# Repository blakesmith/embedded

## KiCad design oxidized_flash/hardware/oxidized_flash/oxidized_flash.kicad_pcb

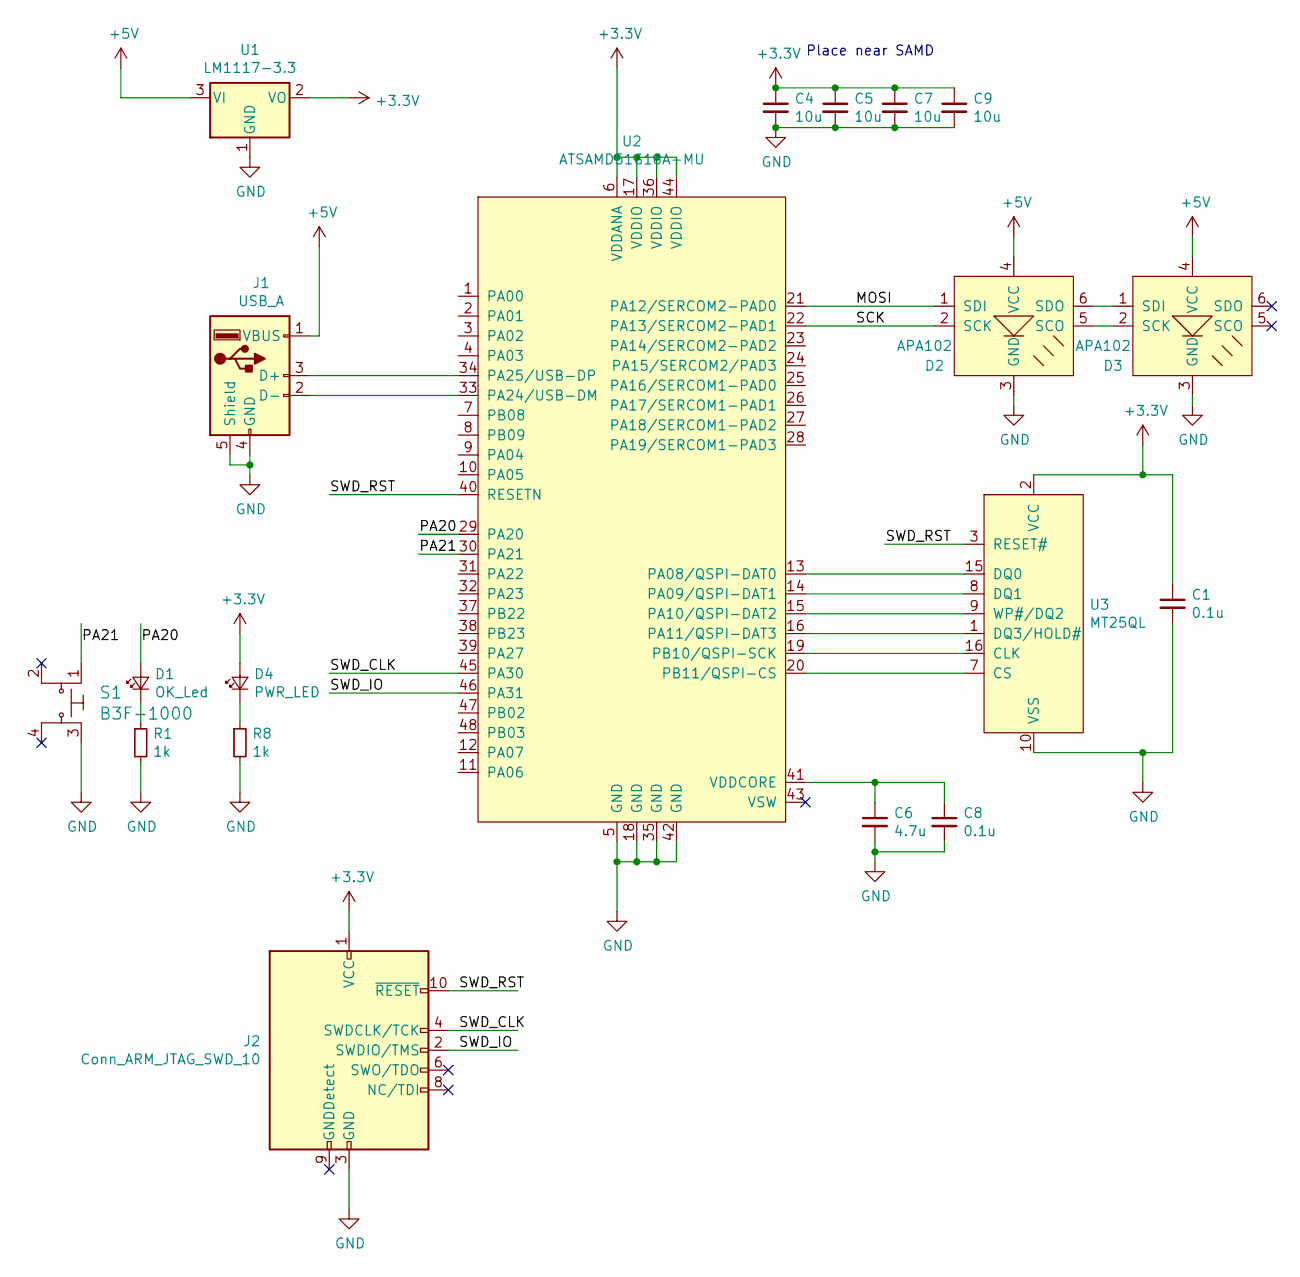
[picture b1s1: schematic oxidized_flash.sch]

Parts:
C1, C8: 0.1u; C_0603_HandSoldering
C4, C5, C7, C9: 10u; C_0603_HandSoldering
C6: 4.7u; C_0603_HandSoldering
D1: OK_Led; LED_0603_HandSoldering
D2, D3: APA102; LED_RGB_5050-6
D4: PWR_LED; LED_0603_HandSoldering
J1: USB_A; Molex_48037_USB_A_Male
J2: Conn_ARM_JTAG_SWD_10; Pin_Header_Straight_2x05_Pitch1.27mm_SMD
R1, R8: 1k; R_0603_HandSoldering
S1: B3F-1000; SW_TH_Tactile_Omron_B3F-10xx; MPN B3F-1000; Digi-Key_PN SW400-ND
U1: LM1117-3.3; SOT-223
U2: ATSAMD51G18A-MU; QFN-48-1EP_7x7mm_Pitch0.5mm
U3: MT25QL; SOP2-16

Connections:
+3V3: C1.1, C4.1, C5.1, C7.1, C9.1, D4.2 (A), J2.1 (VCC), U1.2 (VO), U2.6 (VDDANA), U2.17 (VDDIO), U2.36 (VDDIO), U2.44 (VDDIO), U3.2 (VCC)
+5V: D2.4 (VCC), D3.4 (VCC), J1.1 (VBUS), U1.3 (VI)
/MOSI: D2.1 (SDI), U2.21 (PA12/SERCOM2-PAD0)
/PA20: D1.2 (A), U2.29 (PA20)
/PA21: S1.1, U2.30 (PA21)
/SCK: D2.2 (SCK), U2.22 (PA13/SERCOM2-PAD1)
/SWD_CLK: J2.4 (SWDCLK/TCK), U2.45 (PA30)
/SWD_IO: J2.2 (SWDIO/TMS), U2.46 (PA31)
/SWD_RST: J2.10 (~RESET~), U2.40 (RESETN), U3.3 (RESET#)
GND: C1.2, C4.2, C5.2, C6.2, C7.2, C8.2, C9.2, D2.3 (GND), D3.3 (GND), J1.4 (GND), J1.5 (Shield), J2.3 (GND), J2.5 (GND), R1.2, R8.2, S1.3, U1.1 (GND), U2.5 (GND), U2.18 (GND), U2.35 (GND), U2.42 (GND), U3.10 (VSS)
unnamed: C6.1, C8.1, U2.41 (VDDCORE)
unnamed: D1.1 (K), R1.1
unnamed: D2.5 (SCO), D3.2 (SCK)
unnamed: D2.6 (SDO), D3.1 (SDI)
unnamed: D4.1 (K), R8.1
unnamed: J1.2 (D-), U2.33 (PA24/USB-DM)
unnamed: J1.3 (D+), U2.34 (PA25/USB-DP)
unnamed: U2.13 (PA08/QSPI-DAT0), U3.15 (DQ0)
unnamed: U2.14 (PA09/QSPI-DAT1), U3.8 (DQ1)
unnamed: U2.15 (PA10/QSPI-DAT2), U3.9 (WP#/DQ2)
unnamed: U2.16 (PA11/QSPI-DAT3), U3.1 (DQ3/HOLD#)
unnamed: U2.19 (PB10/QSPI-SCK), U3.16 (CLK)
unnamed: U2.20 (PB11/QSPI-CS), U3.7 (CS)

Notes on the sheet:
Place near SAMD

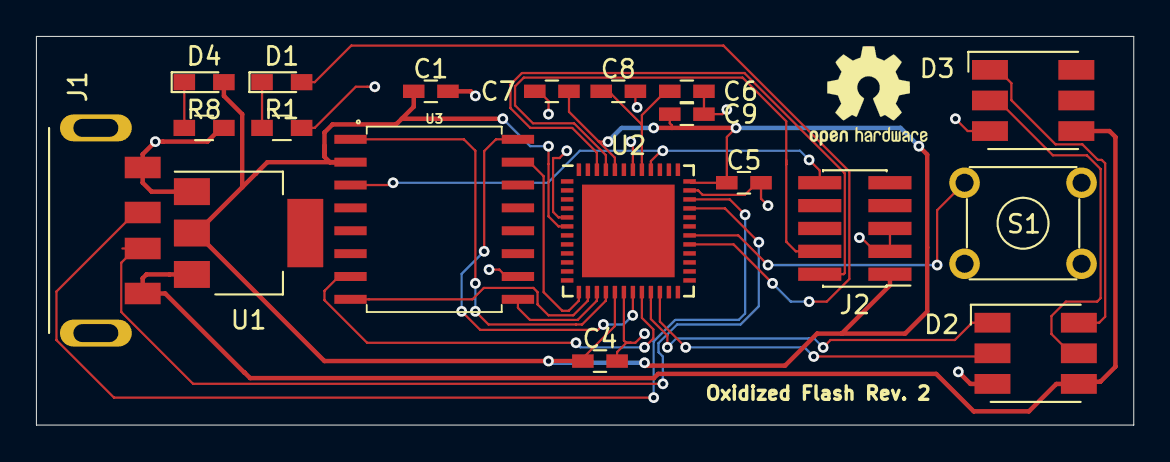
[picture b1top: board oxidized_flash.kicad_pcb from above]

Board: 2 copper layers, 61.0 x 21.6 mm, 19 parts (0 on the bottom side), 23 nets.

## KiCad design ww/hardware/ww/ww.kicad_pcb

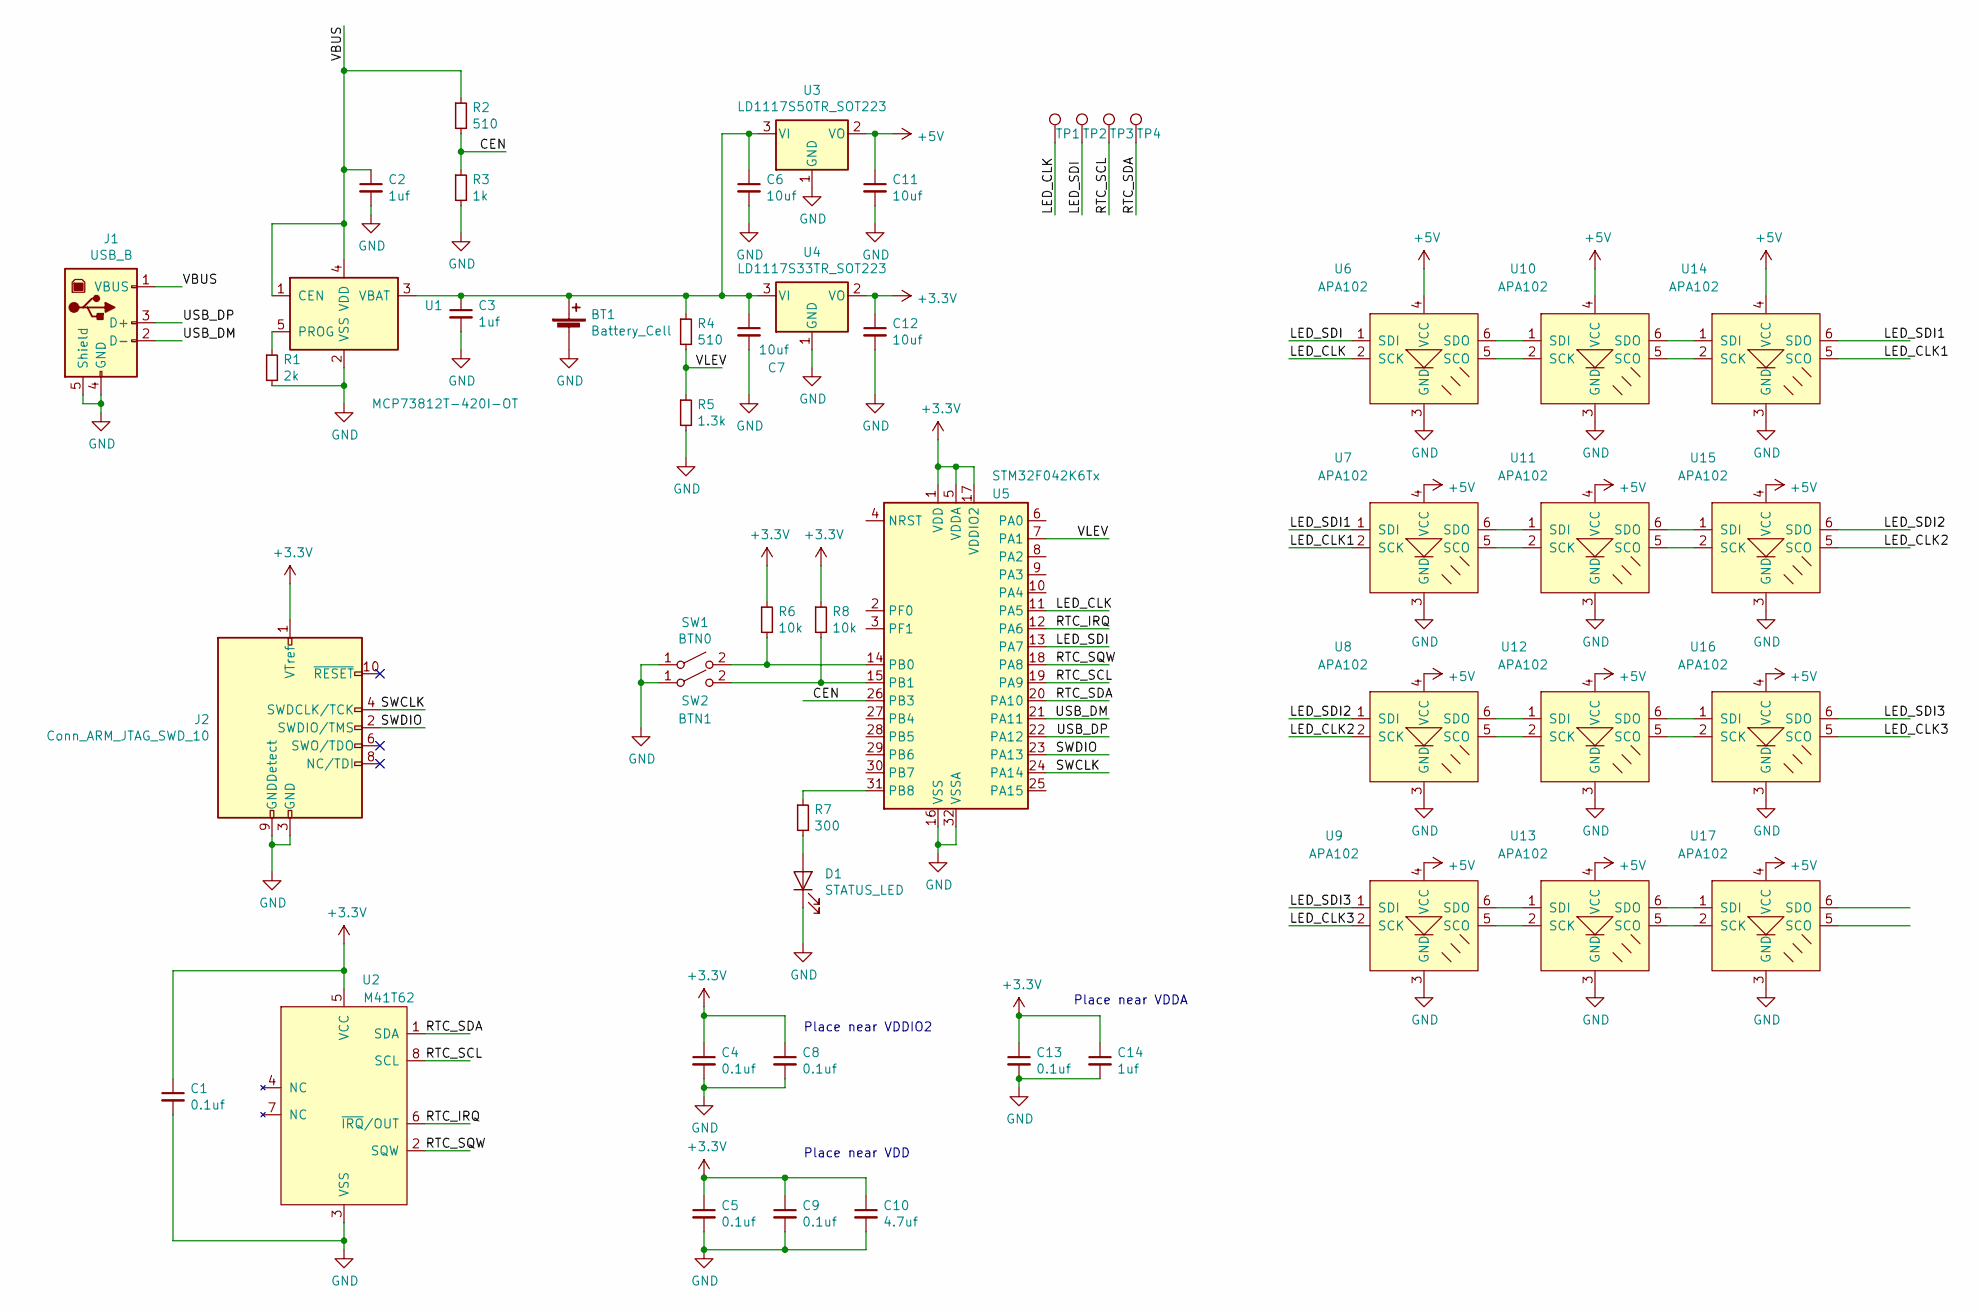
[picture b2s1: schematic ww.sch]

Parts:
BT1: Battery_Cell; JST_PH_S2B-PH-SM4-TB_02x2.00mm_Angled
C1, C4, C5, C8, C9, C13: 0.1uf; C_0603
C2, C3, C14: 1uf; C_0603
C6, C7, C11, C12: 10uf; C_0603
C10: 4.7uf; C_0603
D1: STATUS_LED; D_0603
J1: USB_B; USB_Micro-B_Molex-105017-0001
J2: Conn_ARM_JTAG_SWD_10; Pin_Header_Straight_2x05_Pitch1.27mm_SMD
R1: 2k; R_0603
R2, R4: 510; R_0603
R3: 1k; R_0603
R5: 1.3k; R_0603
R6, R8: 10k; R_0603
R7: 300; R_0603
SW1: BTN0; SW_SPST_EVQP0
SW2: BTN1; SW_SPST_EVQP0
TP1, TP2, TP3, TP4: TestPoint; Test_Point_Pad_1.0x1.0mm
U1: MCP73812T-420I-OT; SOT-23-5
U2: M41T62; PLCC-8_NoSilk
U3: LD1117S50TR_SOT223; SOT-223
U4: LD1117S33TR_SOT223; SOT-223
U5: STM32F042K6Tx; LQFP-32_7x7mm_Pitch0.8mm
U6, U7, U8, U9, U10, U11, U12, U13, U14, U15, U16, U17: APA102; APA102-2020

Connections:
+3V3: C1.1, C4.1, C5.1, C8.1, C9.1, C10.1, C12.1, C13.1, C14.1, J2.1 (VTref), R6.1, R8.1, U2.5 (VCC), U4.2 (VO), U5.1 (VDD), U5.5 (VDDA), U5.17 (VDDIO2)
+5V: C11.1, U3.2 (VO), U6.4 (VCC), U7.4 (VCC), U8.4 (VCC), U9.4 (VCC), U10.4 (VCC), U11.4 (VCC), U12.4 (VCC), U13.4 (VCC), U14.4 (VCC), U15.4 (VCC), U16.4 (VCC), U17.4 (VCC)
/CEN: R2.2, R3.1, U5.26 (PB3)
/LED_CLK: TP1.1, U5.11 (PA5), U6.2 (SCK)
/LED_CLK1: U7.2 (SCK), U14.5 (SCO)
/LED_CLK2: U8.2 (SCK), U15.5 (SCO)
/LED_CLK3: U9.2 (SCK), U16.5 (SCO)
/LED_SDI: TP2.1, U5.13 (PA7), U6.1 (SDI)
/LED_SDI1: U7.1 (SDI), U14.6 (SDO)
/LED_SDI2: U8.1 (SDI), U15.6 (SDO)
/LED_SDI3: U9.1 (SDI), U16.6 (SDO)
/RTC_IRQ: U2.6 (~IRQ~/OUT), U5.12 (PA6)
/RTC_SCL: TP3.1, U2.8 (SCL), U5.19 (PA9)
/RTC_SDA: TP4.1, U2.1 (SDA), U5.20 (PA10)
/RTC_SQW: U2.2 (SQW), U5.18 (PA8)
/SWCLK: J2.4 (SWDCLK/TCK), U5.24 (PA14)
/SWDIO: J2.2 (SWDIO/TMS), U5.23 (PA13)
/USB_DM: J1.2 (D-), U5.21 (PA11)
/USB_DP: J1.3 (D+), U5.22 (PA12)
/VBUS: C2.1, J1.1 (VBUS), R2.1, U1.1 (CEN), U1.4 (VDD)
/VLEV: R4.2, R5.1, U5.7 (PA1)
GND: BT1.2 (-), C1.2, C2.2, C3.2, C4.2, C5.2, C6.2, C7.2, C8.2, C9.2, C10.2, C11.2, C12.2, C13.2, C14.2, D1.1 (K), J1.4 (GND), J1.5 (Shield), J2.3 (GND), J2.5 (GND), J2.9 (GNDDetect), R1.2, R3.2, R5.2, SW1.1 (A), SW2.1 (A), U1.2 (VSS), U2.3 (VSS), U3.1 (GND), U4.1 (GND), U5.16 (VSS), U5.32 (VSSA), U6.3 (GND), U7.3 (GND), U8.3 (GND), U9.3 (GND), U10.3 (GND), U11.3 (GND), U12.3 (GND), U13.3 (GND), U14.3 (GND), U15.3 (GND), U16.3 (GND), U17.3 (GND)
unnamed: BT1.1 (+), C3.1, C6.1, C7.1, R4.1, U1.3 (VBAT), U3.3 (VI), U4.3 (VI)
unnamed: D1.2 (A), R7.2
unnamed: R1.1, U1.5 (PROG)
unnamed: R6.2, SW1.2 (B), U5.14 (PB0)
unnamed: R7.1, U5.31 (PB8)
unnamed: R8.2, SW2.2 (B), U5.15 (PB1)
unnamed: U6.6 (SDO), U10.1 (SDI)
unnamed: U6.5 (SCO), U10.2 (SCK)
unnamed: U10.5 (SCO), U14.2 (SCK)
unnamed: U10.6 (SDO), U14.1 (SDI)
unnamed: U7.6 (SDO), U11.1 (SDI)
unnamed: U7.5 (SCO), U11.2 (SCK)
unnamed: U11.5 (SCO), U15.2 (SCK)
unnamed: U11.6 (SDO), U15.1 (SDI)
unnamed: U8.6 (SDO), U12.1 (SDI)
unnamed: U8.5 (SCO), U12.2 (SCK)
unnamed: U12.5 (SCO), U16.2 (SCK)
unnamed: U12.6 (SDO), U16.1 (SDI)
unnamed: U9.6 (SDO), U13.1 (SDI)
unnamed: U9.5 (SCO), U13.2 (SCK)
unnamed: U13.5 (SCO), U17.2 (SCK)
unnamed: U13.6 (SDO), U17.1 (SDI)

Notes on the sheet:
Place near VDD
Place near VDDIO2
Place near VDDA

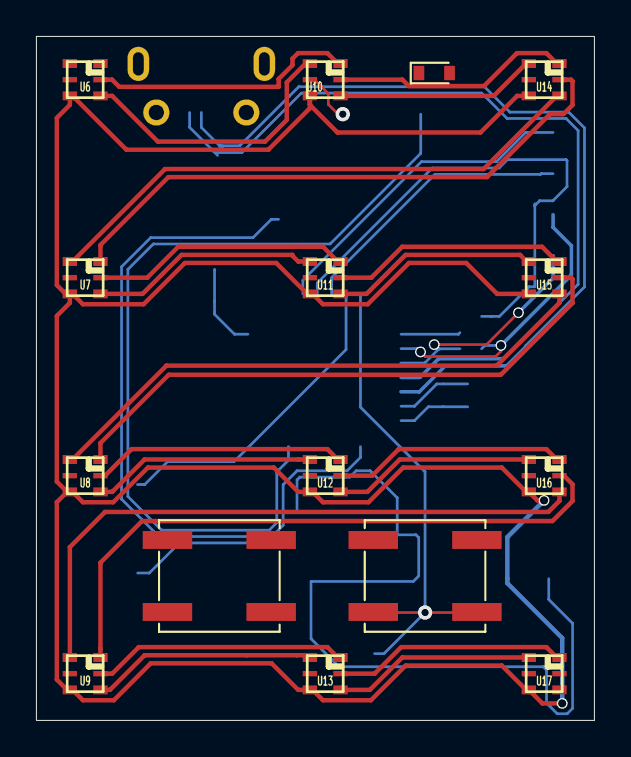
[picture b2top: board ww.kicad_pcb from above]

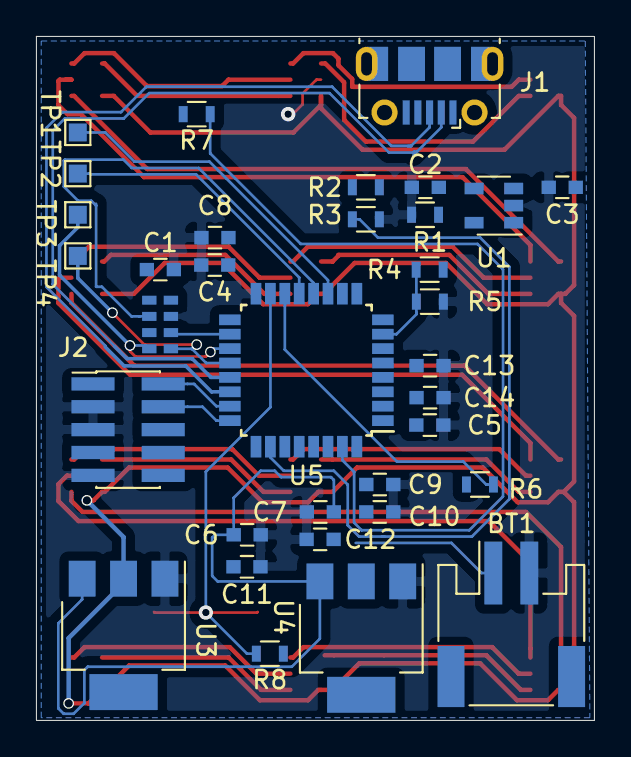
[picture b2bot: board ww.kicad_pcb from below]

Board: 2 copper layers, 31.0 x 38.0 mm, 49 parts (34 on the bottom side), 44 nets.

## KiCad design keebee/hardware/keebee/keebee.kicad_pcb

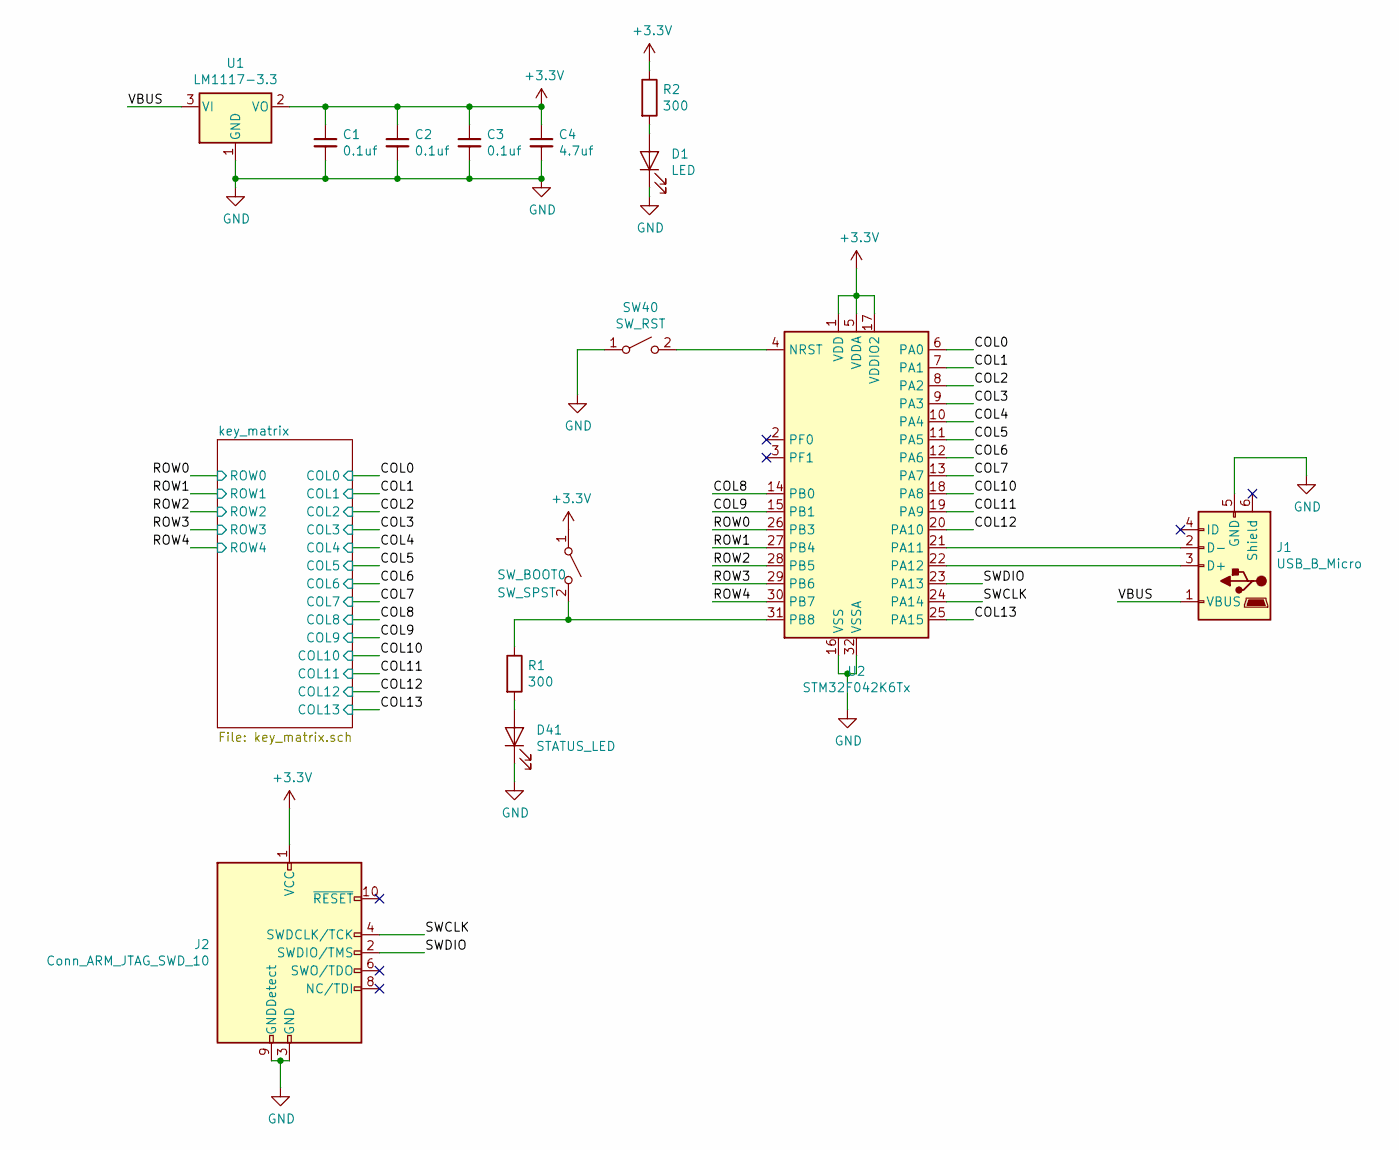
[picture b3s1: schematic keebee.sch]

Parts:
C1, C2, C3: 0.1uf; C_0805_HandSoldering
C4: 4.7uf; C_0805_HandSoldering
D1: LED; LED_0805_HandSoldering
D41: STATUS_LED; LED_0805_HandSoldering
J1: USB_B_Micro; 10118192-0001LF
J2: Conn_ARM_JTAG_SWD_10; Pin_Header_Straight_2x05_Pitch1.27mm_SMD
R1, R2: 300; R_0805_HandSoldering
SW40: SW_RST; SW_PUSH_6mm
SW_BOOT0: SW_SPST; SW_PUSH_6mm
U1: LM1117-3.3; SOT-223
U2: STM32F042K6Tx; LQFP-32_7x7mm_Pitch0.8mm

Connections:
+3V3: C1.1, C2.1, C3.1, C4.1, J2.1 (VCC), R2.1, SW_BOOT0.1 (A), U1.2 (VO), U2.1 (VDD), U2.5 (VDDA), U2.17 (VDDIO2)
/COL0: U2.6 (PA0); also elsewhere on the board
/COL1: U2.7 (PA1); also elsewhere on the board
/COL2: U2.8 (PA2); also elsewhere on the board
/COL3: U2.9 (PA3); also elsewhere on the board
/COL4: U2.10 (PA4); also elsewhere on the board
/COL5: U2.11 (PA5); also elsewhere on the board
/COL6: U2.12 (PA6); also elsewhere on the board
/COL7: U2.13 (PA7); also elsewhere on the board
/COL8: U2.14 (PB0); also elsewhere on the board
/COL9: U2.15 (PB1); also elsewhere on the board
/COL10: U2.18 (PA8); also elsewhere on the board
/COL11: U2.19 (PA9); also elsewhere on the board
/COL12: U2.20 (PA10); also elsewhere on the board
/COL13: U2.25 (PA15); also elsewhere on the board
/ROW0: U2.26 (PB3); also elsewhere on the board
/ROW1: U2.27 (PB4); also elsewhere on the board
/ROW2: U2.28 (PB5); also elsewhere on the board
/ROW3: U2.29 (PB6); also elsewhere on the board
/ROW4: U2.30 (PB7); also elsewhere on the board
/SWCLK: J2.4 (SWDCLK/TCK), U2.24 (PA14)
/SWDIO: J2.2 (SWDIO/TMS), U2.23 (PA13)
/VBUS: J1.1 (VBUS), U1.3 (VI)
GND: C1.2, C2.2, C3.2, C4.2, D1.1 (K), D41.1 (K), J1.5 (GND), J2.3 (GND), J2.5 (GND), J2.9 (GNDDetect), SW40.1 (A), U1.1 (GND), U2.16 (VSS), U2.32 (VSSA)
unnamed: D1.2 (A), R2.2
unnamed: D41.2 (A), R1.2
unnamed: J1.2 (D-), U2.21 (PA11)
unnamed: J1.3 (D+), U2.22 (PA12)
unnamed: R1.1, SW_BOOT0.2 (B), U2.31 (PB8)
unnamed: SW40.2 (B), U2.4 (NRST)

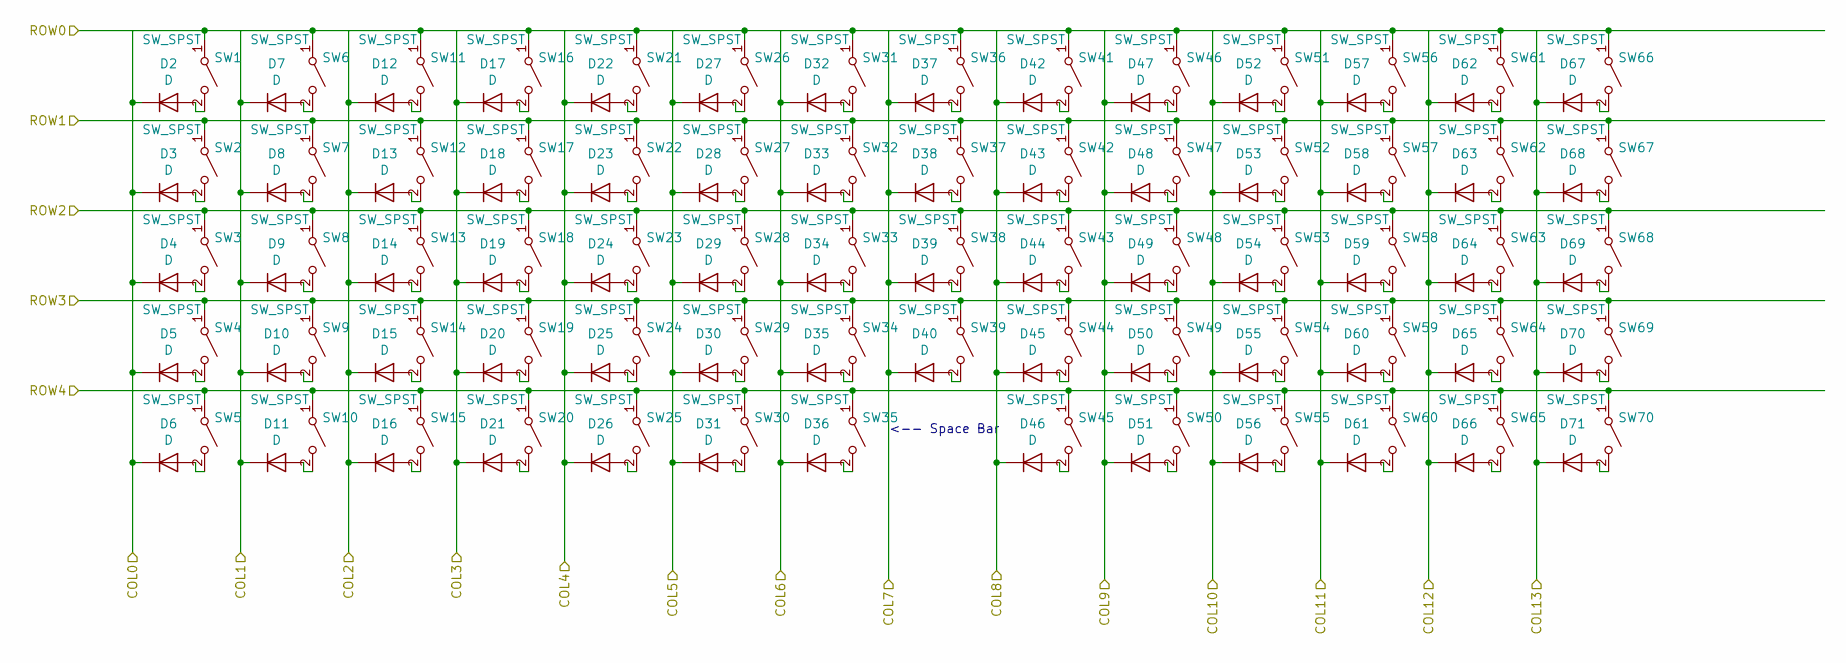
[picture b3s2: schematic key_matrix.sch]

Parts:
D2, D3, D4, D5, D6, D7, D8, D9, D10, D11, D12, D13, D14, D15, D16, D17, D18, D19, D20, D21, D22, D23, D24, D25, D26, D27, D28, D29, D30, D31, D32, D33, D34, D35, D36, D37, D38, D39, D40, D42, D43, D44, D45, D46, D47, D48, D49, D50, D51, D52, D53, D54, D55, D56, D57, D58, D59, D60, D61, D62, D63, D64, D65, D66, D67, D68, D69, D70, D71: D; D_SOD-123
SW1, SW2, SW3, SW4, SW5, SW6, SW7, SW8, SW9, SW10, SW11, SW12, SW13, SW14, SW15, SW16, SW17, SW18, SW19, SW20, SW21, SW22, SW23, SW24, SW25, SW26, SW27, SW28, SW29, SW30, SW31, SW32, SW33, SW34, SW36, SW37, SW38, SW39, SW41, SW42, SW43, SW44, SW45, SW46, SW47, SW48, SW49, SW50, SW51, SW52, SW53, SW54, SW55, SW56, SW57, SW58, SW59, SW60, SW61, SW62, SW63, SW64, SW65, SW66, SW67, SW68, SW69, SW70: SW_SPST; SW_Cherry_MX1A_1.00u_Plate
SW35: SW_SPST; SW_Cherry_MX1A_2.00u_Plate

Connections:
/COL0: D2.1 (K), D3.1 (K), D4.1 (K), D5.1 (K), D6.1 (K); also elsewhere on the board
/COL1: D7.1 (K), D8.1 (K), D9.1 (K), D10.1 (K), D11.1 (K); also elsewhere on the board
/COL2: D12.1 (K), D13.1 (K), D14.1 (K), D15.1 (K), D16.1 (K); also elsewhere on the board
/COL3: D17.1 (K), D18.1 (K), D19.1 (K), D20.1 (K), D21.1 (K); also elsewhere on the board
/COL4: D22.1 (K), D23.1 (K), D24.1 (K), D25.1 (K), D26.1 (K); also elsewhere on the board
/COL5: D27.1 (K), D28.1 (K), D29.1 (K), D30.1 (K), D31.1 (K); also elsewhere on the board
/COL6: D32.1 (K), D33.1 (K), D34.1 (K), D35.1 (K), D36.1 (K); also elsewhere on the board
/COL7: D37.1 (K), D38.1 (K), D39.1 (K), D40.1 (K); also elsewhere on the board
/COL8: D42.1 (K), D43.1 (K), D44.1 (K), D45.1 (K), D46.1 (K); also elsewhere on the board
/COL9: D47.1 (K), D48.1 (K), D49.1 (K), D50.1 (K), D51.1 (K); also elsewhere on the board
/COL10: D52.1 (K), D53.1 (K), D54.1 (K), D55.1 (K), D56.1 (K); also elsewhere on the board
/COL11: D57.1 (K), D58.1 (K), D59.1 (K), D60.1 (K), D61.1 (K); also elsewhere on the board
/COL12: D62.1 (K), D63.1 (K), D64.1 (K), D65.1 (K), D66.1 (K); also elsewhere on the board
/COL13: D67.1 (K), D68.1 (K), D69.1 (K), D70.1 (K), D71.1 (K); also elsewhere on the board
/ROW0: SW1.1 (A), SW6.1 (A), SW11.1 (A), SW16.1 (A), SW21.1 (A), SW26.1 (A), SW31.1 (A), SW36.1 (A), SW41.1 (A), SW46.1 (A), SW51.1 (A), SW56.1 (A), SW61.1 (A), SW66.1 (A); also elsewhere on the board
/ROW1: SW2.1 (A), SW7.1 (A), SW12.1 (A), SW17.1 (A), SW22.1 (A), SW27.1 (A), SW32.1 (A), SW37.1 (A), SW42.1 (A), SW47.1 (A), SW52.1 (A), SW57.1 (A), SW62.1 (A), SW67.1 (A); also elsewhere on the board
/ROW2: SW3.1 (A), SW8.1 (A), SW13.1 (A), SW18.1 (A), SW23.1 (A), SW28.1 (A), SW33.1 (A), SW38.1 (A), SW43.1 (A), SW48.1 (A), SW53.1 (A), SW58.1 (A), SW63.1 (A), SW68.1 (A); also elsewhere on the board
/ROW3: SW4.1 (A), SW9.1 (A), SW14.1 (A), SW19.1 (A), SW24.1 (A), SW29.1 (A), SW34.1 (A), SW39.1 (A), SW44.1 (A), SW49.1 (A), SW54.1 (A), SW59.1 (A), SW64.1 (A), SW69.1 (A); also elsewhere on the board
/ROW4: SW5.1 (A), SW10.1 (A), SW15.1 (A), SW20.1 (A), SW25.1 (A), SW30.1 (A), SW35.1 (A), SW45.1 (A), SW50.1 (A), SW55.1 (A), SW60.1 (A), SW65.1 (A), SW70.1 (A); also elsewhere on the board
unnamed: D2.2 (A), SW1.2 (B)
unnamed: D3.2 (A), SW2.2 (B)
unnamed: D4.2 (A), SW3.2 (B)
unnamed: D5.2 (A), SW4.2 (B)
unnamed: D6.2 (A), SW5.2 (B)
unnamed: D7.2 (A), SW6.2 (B)
unnamed: D8.2 (A), SW7.2 (B)
unnamed: D9.2 (A), SW8.2 (B)
unnamed: D10.2 (A), SW9.2 (B)
unnamed: D11.2 (A), SW10.2 (B)
unnamed: D12.2 (A), SW11.2 (B)
unnamed: D13.2 (A), SW12.2 (B)
unnamed: D14.2 (A), SW13.2 (B)
unnamed: D15.2 (A), SW14.2 (B)
unnamed: D16.2 (A), SW15.2 (B)
unnamed: D17.2 (A), SW16.2 (B)
unnamed: D18.2 (A), SW17.2 (B)
unnamed: D19.2 (A), SW18.2 (B)
unnamed: D20.2 (A), SW19.2 (B)
unnamed: D21.2 (A), SW20.2 (B)
unnamed: D22.2 (A), SW21.2 (B)
unnamed: D23.2 (A), SW22.2 (B)
unnamed: D24.2 (A), SW23.2 (B)
unnamed: D25.2 (A), SW24.2 (B)
unnamed: D26.2 (A), SW25.2 (B)
unnamed: D27.2 (A), SW26.2 (B)
unnamed: D28.2 (A), SW27.2 (B)
unnamed: D29.2 (A), SW28.2 (B)
unnamed: D30.2 (A), SW29.2 (B)
unnamed: D31.2 (A), SW30.2 (B)
unnamed: D32.2 (A), SW31.2 (B)
unnamed: D33.2 (A), SW32.2 (B)
unnamed: D34.2 (A), SW33.2 (B)
unnamed: D35.2 (A), SW34.2 (B)
unnamed: D36.2 (A), SW35.2 (B)
unnamed: D37.2 (A), SW36.2 (B)
unnamed: D38.2 (A), SW37.2 (B)
unnamed: D39.2 (A), SW38.2 (B)
unnamed: D40.2 (A), SW39.2 (B)
unnamed: D42.2 (A), SW41.2 (B)
unnamed: D43.2 (A), SW42.2 (B)
unnamed: D44.2 (A), SW43.2 (B)
unnamed: D45.2 (A), SW44.2 (B)
unnamed: D46.2 (A), SW45.2 (B)
unnamed: D47.2 (A), SW46.2 (B)
unnamed: D48.2 (A), SW47.2 (B)
unnamed: D49.2 (A), SW48.2 (B)
unnamed: D50.2 (A), SW49.2 (B)
unnamed: D51.2 (A), SW50.2 (B)
unnamed: D52.2 (A), SW51.2 (B)
unnamed: D53.2 (A), SW52.2 (B)
unnamed: D54.2 (A), SW53.2 (B)
unnamed: D55.2 (A), SW54.2 (B)
unnamed: D56.2 (A), SW55.2 (B)
unnamed: D57.2 (A), SW56.2 (B)
unnamed: D58.2 (A), SW57.2 (B)
unnamed: D59.2 (A), SW58.2 (B)
unnamed: D60.2 (A), SW59.2 (B)
unnamed: D61.2 (A), SW60.2 (B)
unnamed: D62.2 (A), SW61.2 (B)
unnamed: D63.2 (A), SW62.2 (B)
unnamed: D64.2 (A), SW63.2 (B)
unnamed: D65.2 (A), SW64.2 (B)
unnamed: D66.2 (A), SW65.2 (B)
unnamed: D67.2 (A), SW66.2 (B)
unnamed: D68.2 (A), SW67.2 (B)
unnamed: D69.2 (A), SW68.2 (B)
unnamed: D70.2 (A), SW69.2 (B)
unnamed: D71.2 (A), SW70.2 (B)

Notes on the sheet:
<-- Space Bar

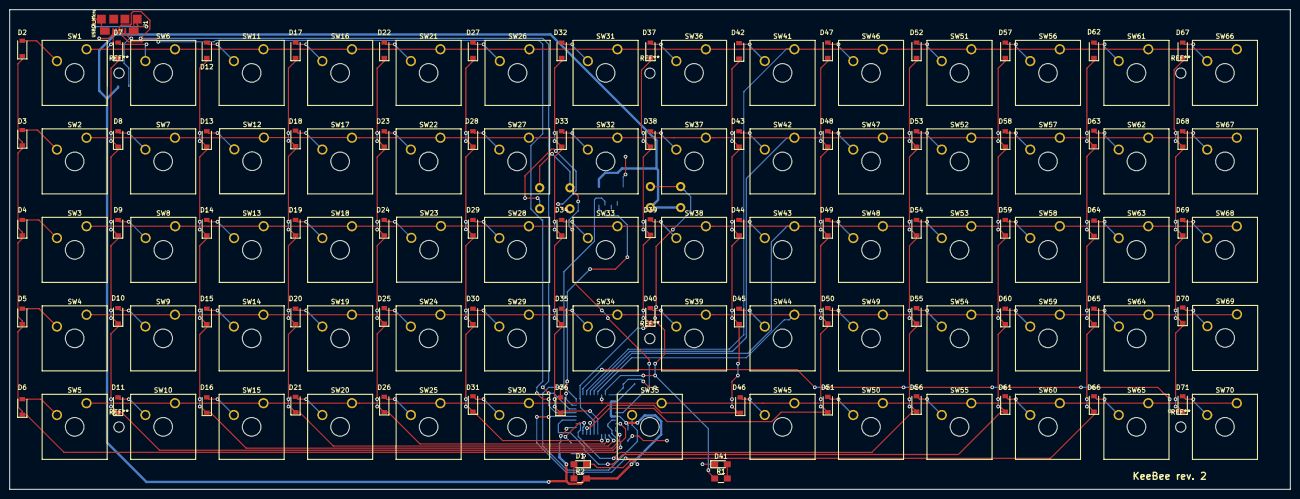
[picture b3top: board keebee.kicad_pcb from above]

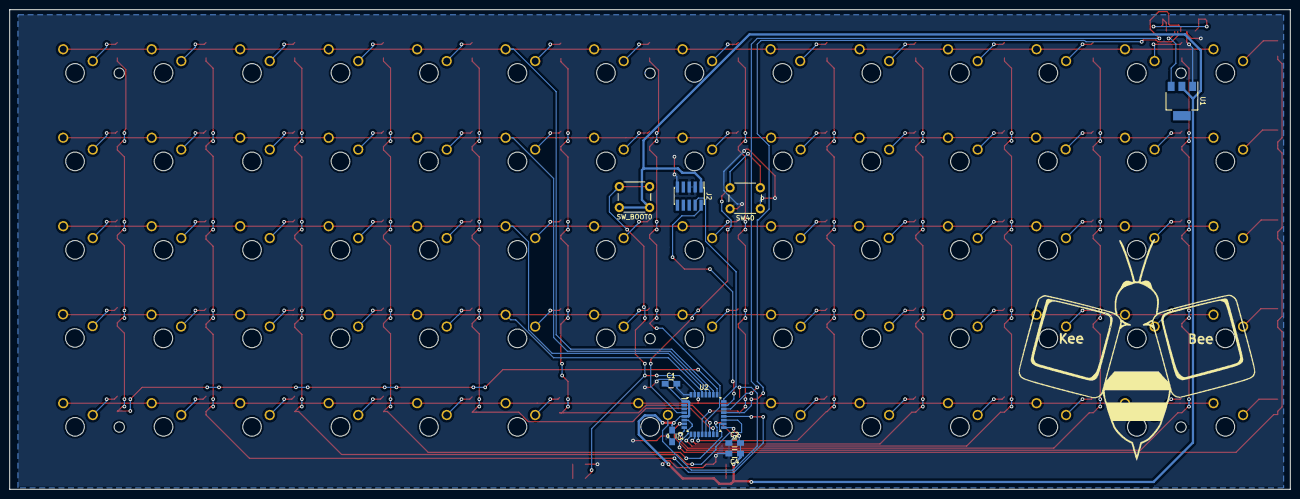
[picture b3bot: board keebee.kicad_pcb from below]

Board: 2 copper layers, 275.0 x 103.0 mm, 152 parts (9 on the bottom side), 99 nets.

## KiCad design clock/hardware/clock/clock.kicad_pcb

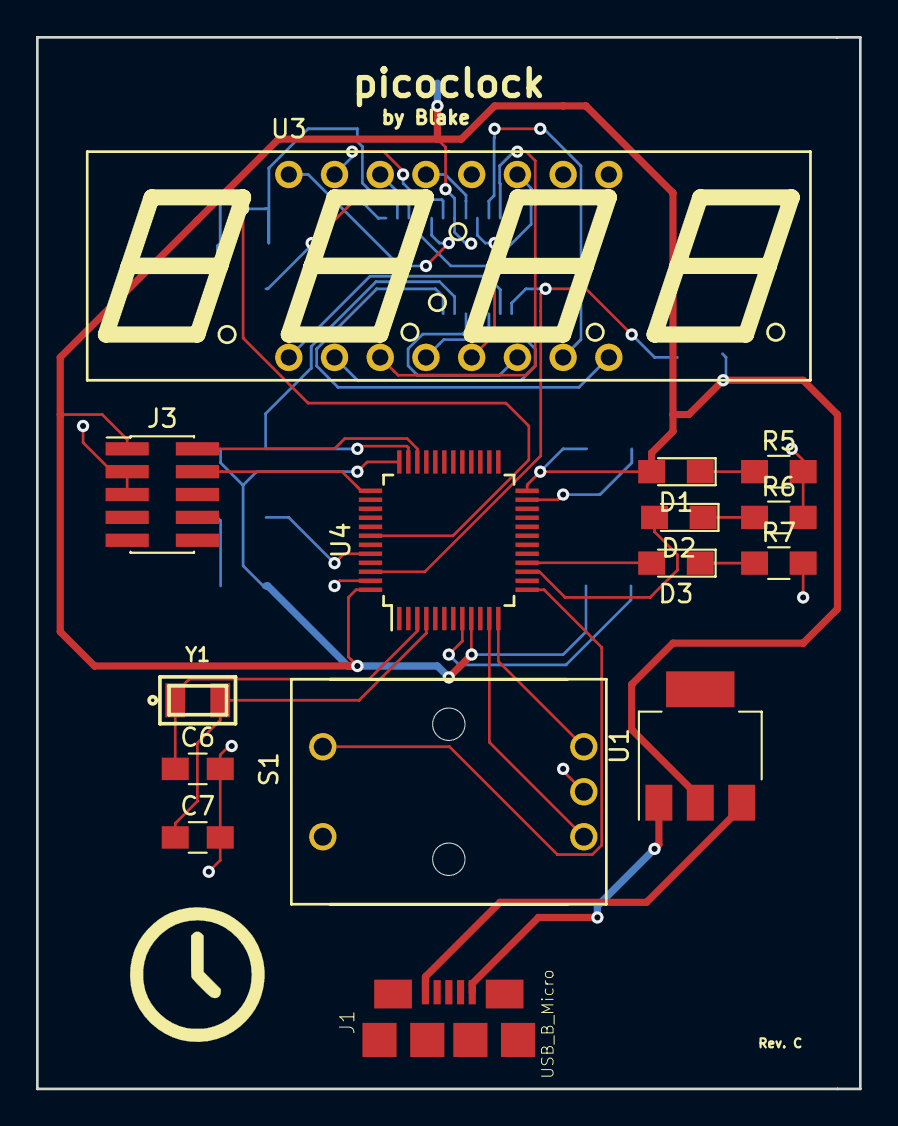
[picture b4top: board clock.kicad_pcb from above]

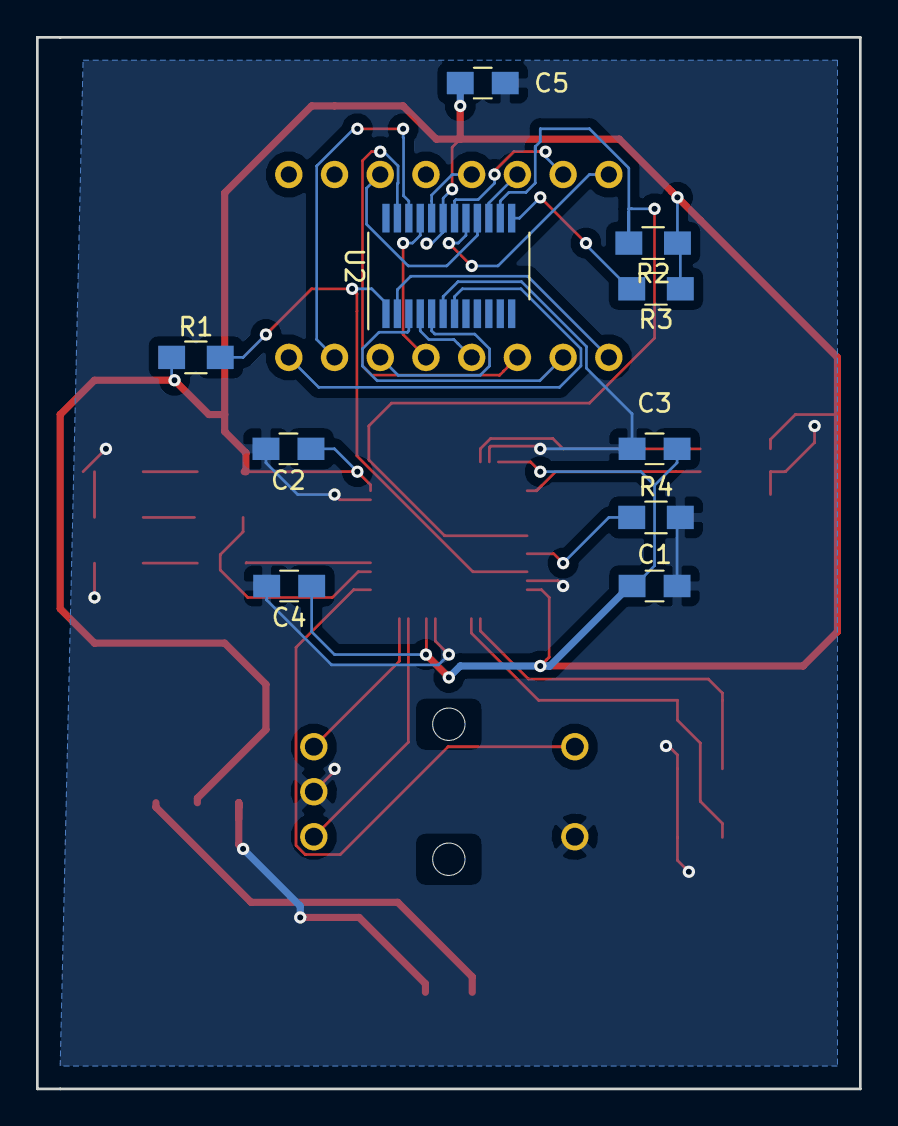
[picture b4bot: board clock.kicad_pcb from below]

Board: 2 copper layers, 45.7 x 58.4 mm, 25 parts (10 on the bottom side), 32 nets.

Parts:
C1, C2, C3, C4: 0.1uf; C_0805_HandSoldering
C5: 0.1uF; C_0805_HandSoldering
C6, C7: 10pf; C_0805_HandSoldering
D1: LED Blue; LED_0805_HandSoldering
D2: LED Green; LED_0805_HandSoldering
D3: LED Red; LED_0805_HandSoldering
J1: USB_B_Micro; 10118192-0001LF
J3: Conn_ARM_JTAG_SWD_10; Pin_Header_Straight_2x05_Pitch1.27mm_SMD
R1, R2: 10K; R_0805_HandSoldering
R3, R4: 10k; R_0805_HandSoldering
R5, R6, R7: 300; R_0805_HandSoldering
S1: PEC11R; PEC11
U1: LM1117-3.3; SOT-223
U2: AS1115; QSOP-24_3.9x8.7mm_Pitch0.635mm
U3: LTC-4727JS; LTC-4727
U4: STM32L151C8TxA; LQFP-48_7x7mm_Pitch0.5mm
Y1: 32.768kHz; ECS-31B_xtal

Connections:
+3V3: C1.1, C2.1, C3.1, C4.1, C5.1, D1.2, J3.1, R1.1, R2.1, R3.1, U1.2, U2.19, U4.9, U4.24, U4.36, U4.48
/7SEG_SCL: R2.2, U2.14, U4.42
/7SEG_SDA: R1.2, U2.1, U4.46
/ENC_BTN: S1.5, U4.13
/ENC_CCW: S1.3, U4.12
/ENC_CW: S1.1, U4.11
/JTAG_TCK: J3.4, U4.37
/JTAG_TMS: J3.2, U4.34
/STATUS_ERR: D3.2, U4.16
/STATUS_OK: D2.2, U4.15
GND: C1.2, C2.2, C3.2, C4.2, C5.2, C6.2, C7.2, J1.5, J3.3, J3.5, R4.2, R5.2, R6.2, R7.2, S1.2, S1.4, U1.1, U2.6, U4.8, U4.23, U4.35, U4.47
unnamed: C6.1, U4.3, Y1.1
unnamed: C7.1, U4.4, Y1.2
unnamed: D1.1, R5.1
unnamed: D2.1, R6.1
unnamed: D3.1, R7.1
unnamed: J1.1, U1.3
unnamed: R3.2, U2.13
unnamed: R4.1, U4.44
unnamed: U2.2, U3.1
unnamed: U2.3, U3.2
unnamed: U2.4, U3.4
unnamed: U2.5, U3.6
unnamed: U2.7, U3.8
unnamed: U2.15, U3.14
unnamed: U2.16, U3.11
unnamed: U2.17, U3.16
unnamed: U2.18, U3.15
unnamed: U2.20, U3.13
unnamed: U2.21, U3.5
unnamed: U2.22, U3.7
unnamed: U2.23, U3.3

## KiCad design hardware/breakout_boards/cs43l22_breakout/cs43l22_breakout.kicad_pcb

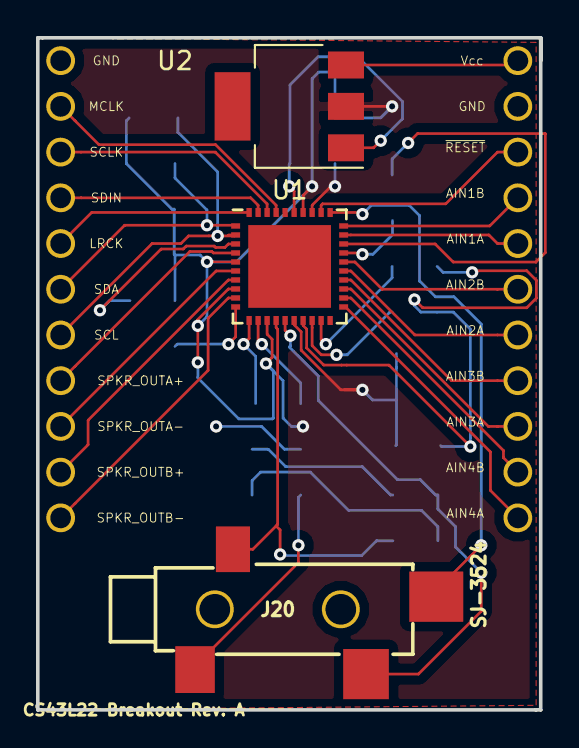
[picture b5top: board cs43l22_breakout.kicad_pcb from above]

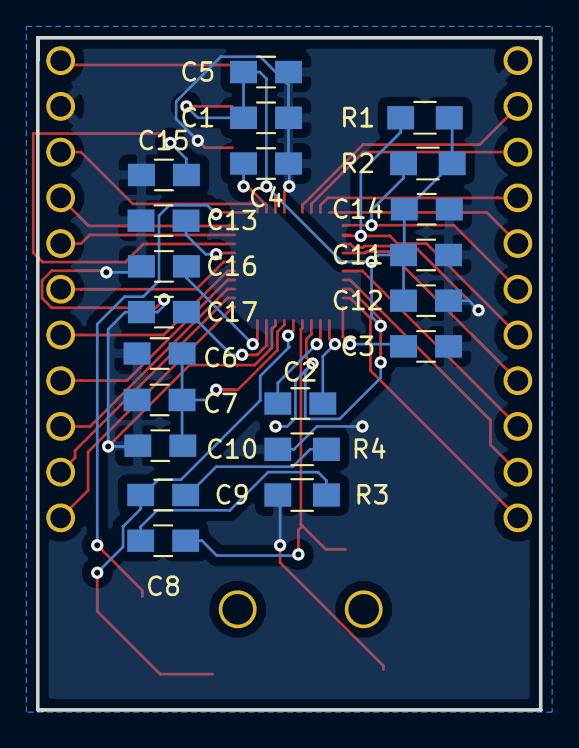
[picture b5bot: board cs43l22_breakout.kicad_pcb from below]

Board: 2 copper layers, 27.9 x 37.3 mm, 45 parts (21 on the bottom side), 33 nets.

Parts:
AIN1A: AIN1A; Conn_1pin_2.54mm
AIN1B: AIN1B; Conn_1pin_2.54mm
AIN2A: AIN2A; Conn_1pin_2.54mm
AIN2B: AIN2B; Conn_1pin_2.54mm
AIN3A: AIN3A; Conn_1pin_2.54mm
AIN3B: AIN3B; Conn_1pin_2.54mm
AIN4A: AIN4A; Conn_1pin_2.54mm
AIN4B: AIN4B; Conn_1pin_2.54mm
C1, C4, C5, C6, C7, C11, C12: 0.1uf; C_0805_HandSoldering
C2, C3, C10, C16: 1uf; C_0805_HandSoldering
C8, C9: 0.022uf; C_0805_HandSoldering
C13, C15: 150pf; C_0805_HandSoldering
C14, C17: 10uf; C_0805_HandSoldering
GND: GND; Conn_1pin_2.54mm
GND#2: GND; Conn_1pin_2.54mm
J20: SJ-3524; SJ-3524-SMT_Stereo_Jack
LRCK: LRCK; Conn_1pin_2.54mm
MCLK: MCLK; Conn_1pin_2.54mm
R1, R2: 10k; R_0805_HandSoldering
R3, R4: 51.1; R_0805_HandSoldering
SCL: SCL; Conn_1pin_2.54mm
SCLK: SCLK; Conn_1pin_2.54mm
SDA: SDA; Conn_1pin_2.54mm
SDIN: SDIN; Conn_1pin_2.54mm
SPKR_OUTA+: SPKR_OUTA+; Conn_1pin_2.54mm
SPKR_OUTA-: SPKR_OUTA-; Conn_1pin_2.54mm
SPKR_OUTB+: SPKR_OUTB+; Conn_1pin_2.54mm
SPKR_OUTB-: SPKR_OUTB-; Conn_1pin_2.54mm
U1: CS43L22_V2; QFN-40-1EP_6x6mm_Pitch0.5mm
U2: LM1117-1.8; SOT-223
Vcc: +5V; Conn_1pin_2.54mm

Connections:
+1V8: C1.1, C4.1, C5.1, C6.1, C7.1, C10.1, C11.1, C12.1, C14.1, R1.2, R2.2, U1.5, U1.8, U1.13, U1.16, U1.33, U1.34, U2.2
GND: C1.2, C3.2, C4.2, C5.2, C6.2, C7.2, C10.2, C11.2, C12.2, C13.1, C14.2, C15.1, C16.1, C17.1, GND.1, GND#2.1, J20.1, R3.1, R4.1, U1.3, U1.17, U1.35, U2.1
unnamed: AIN1A.1, U1.29
unnamed: AIN1B.1, U1.30
unnamed: AIN2A.1, U1.25
unnamed: AIN2B.1, U1.26
unnamed: AIN3A.1, U1.23
unnamed: AIN3B.1, U1.24
unnamed: AIN4A.1, U1.21
unnamed: AIN4B.1, U1.22
unnamed: C2.1, U1.12
unnamed: C2.2, U1.11
unnamed: C3.1, U1.10
unnamed: C8.1, R3.2
unnamed: C8.2, J20.3, U1.14
unnamed: C9.1, R4.2
unnamed: C9.2, J20.2, U1.15
unnamed: C13.2, U1.27
unnamed: C15.2, U1.28
unnamed: C16.2, U1.19
unnamed: C17.2, U1.18
unnamed: J20.4, U1.31
unnamed: LRCK.1, U1.40
unnamed: MCLK.1, U1.37
unnamed: R1.1, SCL.1, U1.2
unnamed: R2.1, SDA.1, U1.1
unnamed: SCLK.1, U1.38
unnamed: SDIN.1, U1.39
unnamed: SPKR_OUTA+.1, U1.4
unnamed: SPKR_OUTA-.1, U1.6
unnamed: SPKR_OUTB+.1, U1.7
unnamed: SPKR_OUTB-.1, U1.9
unnamed: U2.3, Vcc.1
